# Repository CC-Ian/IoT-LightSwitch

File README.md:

# An Open Source "IoT" Lightswitch
This project seeks to implement a wifi connected, computer controlled lightswitch which protects the user's privacy, and has more features than a traditional light switch.

## DANGER! LETHAL VOLTAGES
  
This project is not for the inexperienced. There is exposed AC Mains present on the PCB, and installation requires modifying the AC Mains Connection within a switch box.  

## FIRE HAZARD WARMING
This product is designed to switch on and off a ceiling fan and a light or two. The mains traces are rated at 6A for a 10 degree rise over ambient. Install a 5A fuse in the location on the PCB, and ensure that your load is less than 5A before using this device.

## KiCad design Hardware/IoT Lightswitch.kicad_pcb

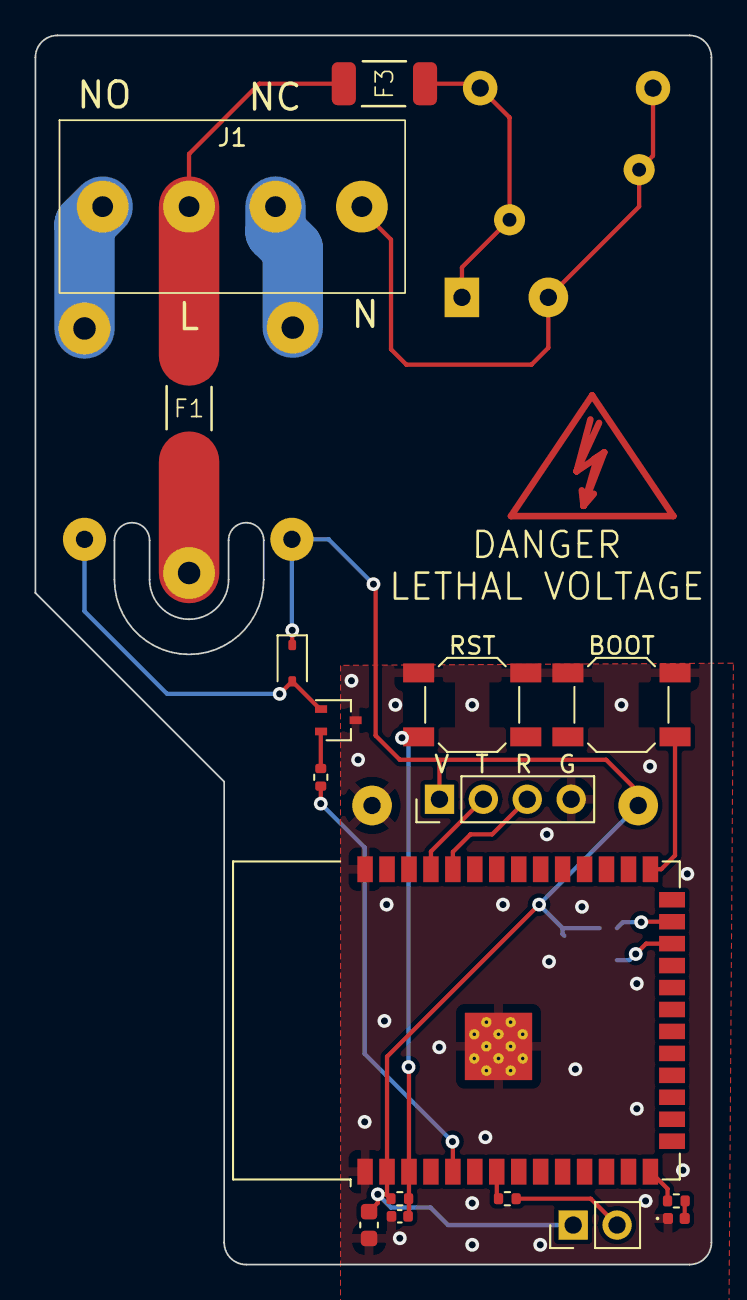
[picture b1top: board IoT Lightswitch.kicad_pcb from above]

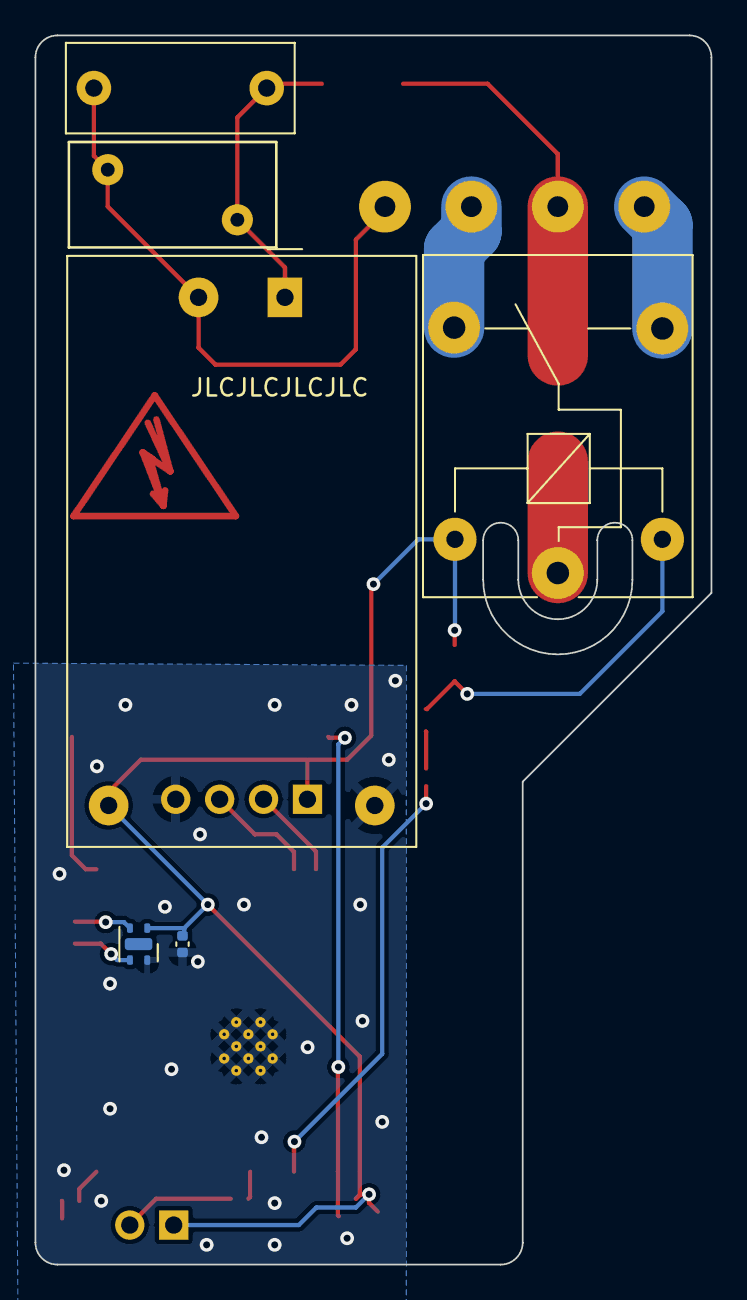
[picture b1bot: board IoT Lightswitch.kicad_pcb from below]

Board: 2 copper layers, 39.1 x 71.1 mm, 23 parts (6 on the bottom side), 21 nets.

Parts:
BOOT: SW_Push; SW_SPST_SKQG_WithStem
C1, C4: 100n; C_0402_1005Metric
C2: 150n; C_Rect_L13.0mm_W5.0mm_P10.00mm_FKS3_FKP3_MKS4
C3: 10u; C_0603_1608Metric
D1: D; D_SOD-323
D2: LED; LED_0402_1005Metric
F1: 5A 250v; Fuse_6125
F3: 0.5A 125v; Fuse_6125
J1: Screw_Terminal_01x04; WJ128V-5.0-2P
K1: SANYOU_SRD_Form_C; Relay_SPDT_SANYOU_SRD_Series_Form_C
PS1: HLK-PM03; Converter_ACDC_HiLink_HLK-PMxx
Q1: NMOS; SOT-323_SC-70
R1, R2, R3: 10k; R_0402_1005Metric
R4: 5k1; R_0402_1005Metric
RST: SW_Push; SW_SPST_SKQG_WithStem
RV1: Varistor; RV_Disc_D12mm_W6.1mm_P7.5mm
SW5: SW_SPST; PinHeader_1x02_P2.54mm_Vertical
U1: ESP32-S2-SOLO-2; ESP32-S3-WROOM-1
U2: SHTC3; Sensirion_DFN-4-1EP_2x2mm_P1mm_EP0.7x1.6mm
V  T  R  G: Conn_01x04; PinHeader_1x04_P2.54mm_Vertical

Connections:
+3V3: C3.1, C4.1, D1.1 (K), K1.2, PS1.4 (+Vout), R1.2, SW5.1 (A), U1.2 (VCC), U2.1 (VDD), V T R G.1
AC_L: F1.1, F3.1, J1.3
AC_L_FUSED: F1.2, K1.1
AC_N: C2.2, J1.1, PS1.2 (AC/N), RV1.2
AC_NC: J1.2, K1.4
AC_NO: J1.4, K1.3
BOOT: BOOT.2, U1.27 (IO0)
GND: BOOT.1, C1.2, C3.2, C4.2, D2.1 (K), PS1.3 (-Vout), Q1.3 (S), RST.2, U1.1 (GND), U1.40 (GND), U1.41 (EPAD), U2.4 (VSS), V T R G.4
IO5: R2.2, U1.5 (IO5)
IO7: R3.2, U1.7 (IO7)
IO20: R4.2, U1.14 (IO20)
unnamed: D1.2 (A), K1.5, Q1.1 (D)
unnamed: D2.2 (A), R4.1
unnamed: C2.1, F3.2, PS1.1 (AC/L), RV1.1
unnamed: Q1.2 (G), R2.1
unnamed: R3.1, SW5.2 (B)
RST: C1.1, R1.1, RST.1, U1.3 (EN)
RX: U1.36 (RX), V T R G.3
SCL: U1.25 (IO34), U2.2 (SCL)
SDA: U1.24 (IO33), U2.3 (SDA)
TX: U1.37 (TX), V T R G.2

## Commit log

2023-04-13 Created Readme
2023-04-13 Update warning color
2023-04-13 Added colored warning logo
2023-04-13 Updated Schema
2023-04-13 Moved PSU Fuse from Neutral to Live
2023-04-14 Added Humidity and Temperature Sensor
